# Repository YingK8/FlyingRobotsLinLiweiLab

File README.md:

# FlyingRobotsLinLiweiLab

A magnetically actuated micro flying robot. A four-coil phased array drives a
rotating field that spins and tilts a passive magnetic rotor; a stereo camera
rig closes the loop on its pose.

| Where | What |
|---|---|
| [`ESP32_PMW/`](ESP32_PMW/README.md) | ESP32 firmware: phased PWM coil drive, current sensing, balance loop |
| [`ESP32_PMW/controller/`](ESP32_PMW/controller/README.md) | the vision → control pipeline (camera → calib → pose → control) |
| `ESP32_PMW/ai/` | sweeps, system ID, validation, instrumentation, plotting |
| `PCB/`, `ESP32_PMW/docs/` | the H-bridge power stage: KiCad sources and the board writeup |
| `3DModels/` | printed frame, coil plate, takeoff rig |
| `calculations/` | coil resonance and capacitor sizing |
| `pico/` | earlier RP2040 current-characterization work (see `pico/PROGRESS.md`) |

Start with [`ESP32_PMW/README.md`](ESP32_PMW/README.md) for the firmware, or
[`ESP32_PMW/controller/README.md`](ESP32_PMW/controller/README.md) for the
control pipeline. Each controller stage carries its own `theory.md` chapter
deriving what it implements.

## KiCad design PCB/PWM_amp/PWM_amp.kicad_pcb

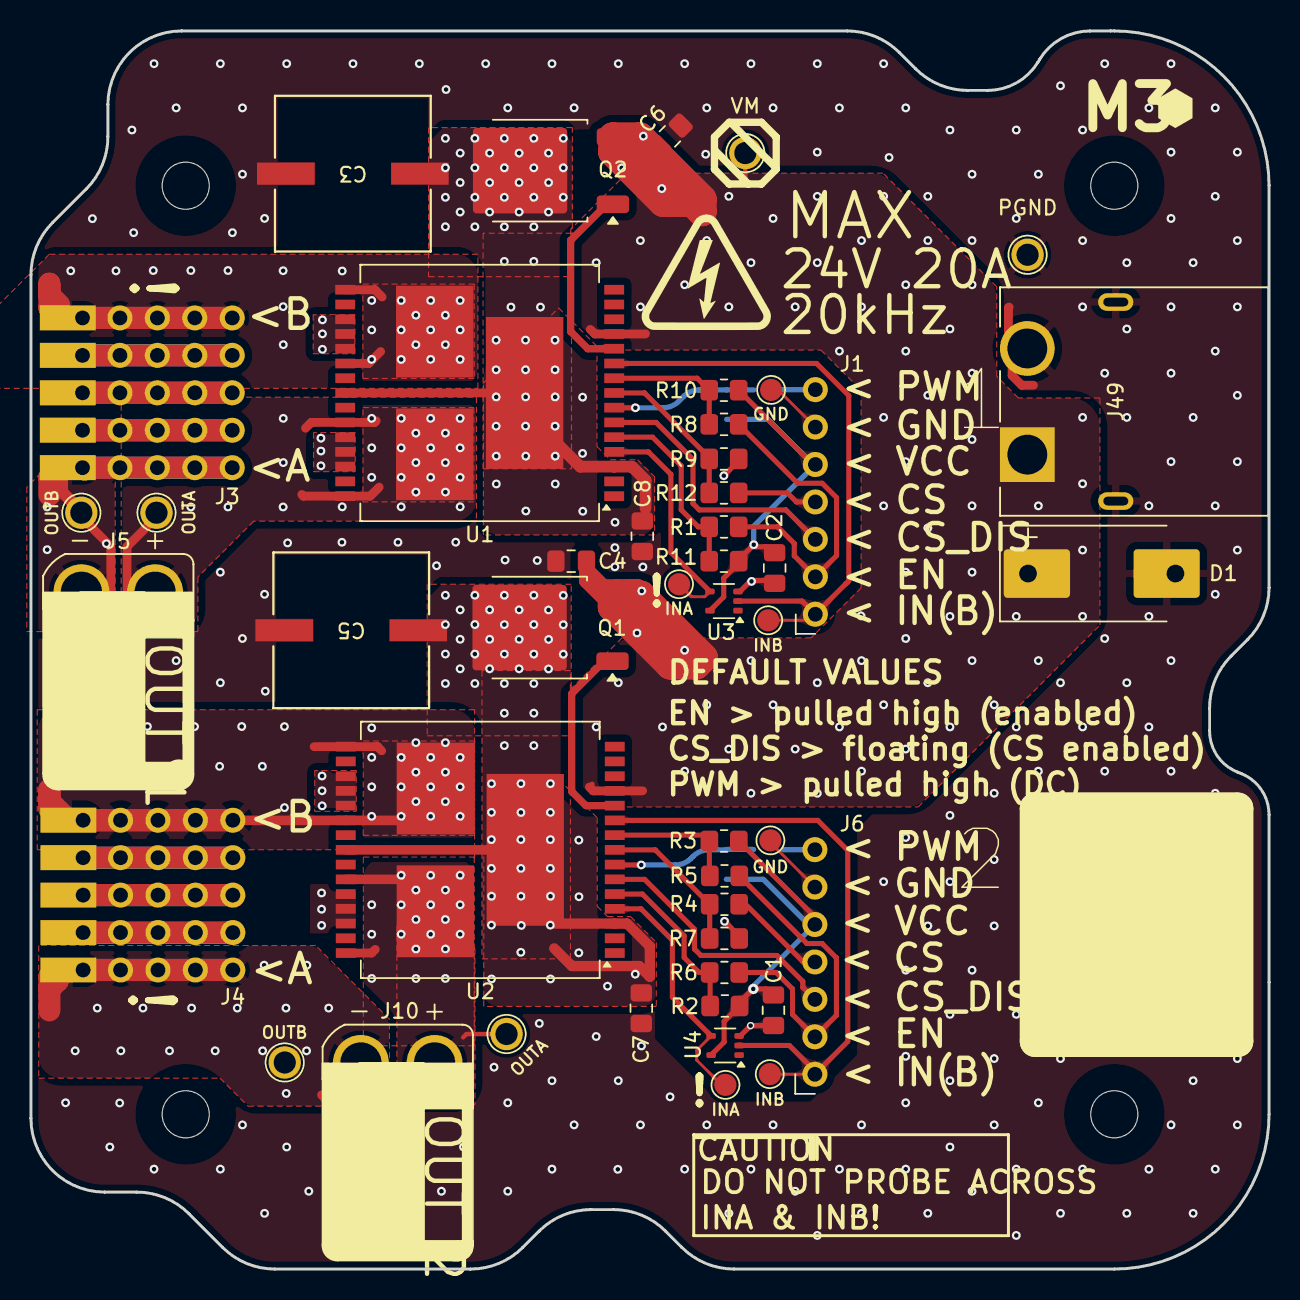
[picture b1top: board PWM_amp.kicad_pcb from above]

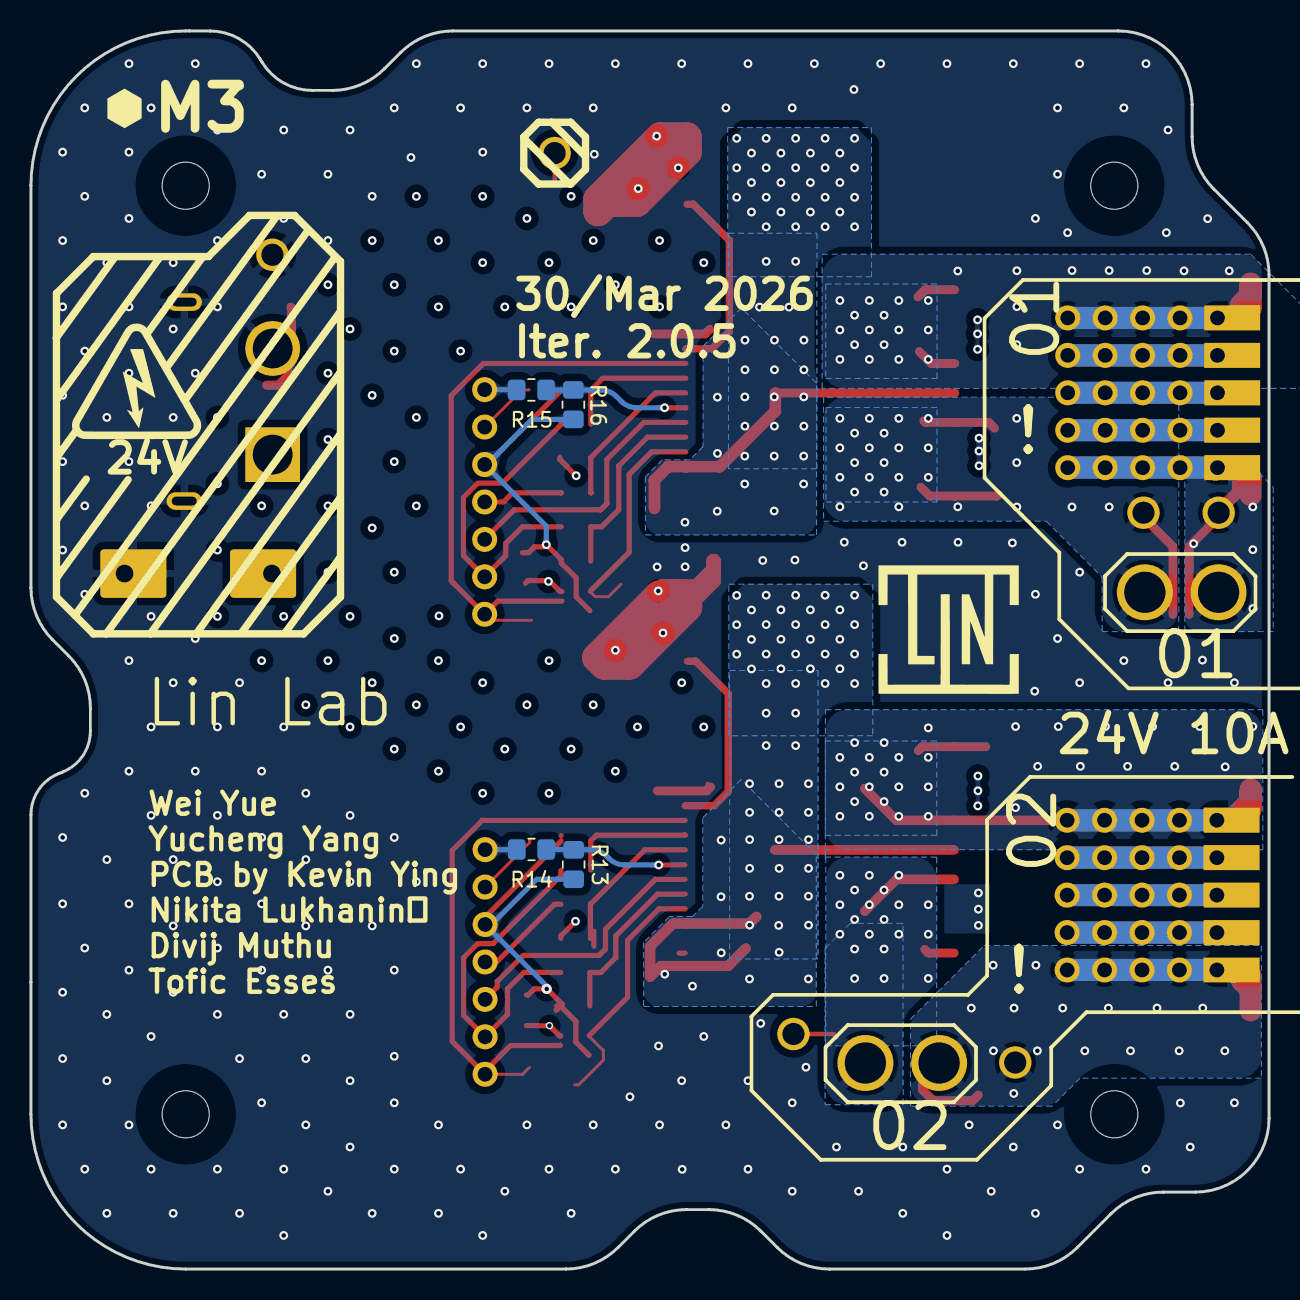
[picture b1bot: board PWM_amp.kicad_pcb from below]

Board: 4 copper layers, 84.0 x 84.0 mm, 54 parts (6 on the bottom side), 34 nets.

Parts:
C1, C2, C7, C8: 0.1uF; C_0805_2012Metric_Pad1.18x1.45mm_HandSolder
C3, C5: 100uF; CAP_EEH-ZC_10P3X10P3_PAN
C4, C6: 1uF; C_0805_2012Metric_Pad1.18x1.45mm_HandSolder
D1: SMCJ18A; D_SMC-RM10_Universal_Handsoldering
GND: TestPoint; TestPoint_Pad_D1.5mm
GND#2: TestPoint; TestPoint_Pad_D1.5mm
H1, H2, H3, H8: MountingHole; MountingHole_3.2mm_M3
INA: TestPoint; TestPoint_Pad_D1.5mm
INA#2: TestPoint; TestPoint_Pad_D1.5mm
INB: TestPoint; TestPoint_Pad_D1.5mm
INB#2: TestPoint; TestPoint_Pad_D1.5mm
J1, J6: Conn_01x07_Pin; PinSocket_1x07_P2.54mm_Vertical
J3, J4: Conn_01x02_Pin; matrix5x5
J5, J10: XT30UPB-M; xt30
J49: XT60PW-M; AMASS_XT60PW-M
OUTA: TestPoint; TestPoint_THTPad_D3.0mm_Drill1.5mm
OUTA#2: TestPoint; TestPoint_THTPad_D3.0mm_Drill1.5mm
OUTB: TestPoint; TestPoint_THTPad_D3.0mm_Drill1.5mm
OUTB#2: TestPoint; TestPoint_THTPad_D3.0mm_Drill1.5mm
PGND: TestPoint; TestPoint_THTPad_D3.0mm_Drill1.5mm
Q1, Q2: FDD8447L; TO-252-2
R1, R5, R6, R7, R8, R9: 1k; R_0805_2012Metric_Pad1.20x1.40mm_HandSolder
R2, R3, R4, R10, R11, R12, R13, R16: 4.7k; R_0805_2012Metric_Pad1.20x1.40mm_HandSolder
R14, R15: 100; R_0805_2012Metric_Pad1.20x1.40mm_HandSolder
U1, U2: VNH5019A-E; ST_MultiPowerSO-30
U3, U4: NC7SVU04P5X; SOT-353_SC-70-5
VM: TestPoint; TestPoint_THTPad_D3.0mm_Drill1.5mm

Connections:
+3V_1: C1.1, C2.1, J1.5, J6.5, R2.2, R3.2, R10.2, R11.2, R13.2, R16.2, U3.5 (VCC), U4.5 (VCC)
GND1: C1.2, C2.2, GND.1, GND#2.1, J1.6, J6.6, R7.1, R9.1, U3.3 (GND), U4.3 (GND)
INA1: INA.1, U2.4 (INA), U4.4
INA2: INA#2.1, U1.4 (INA), U3.4
INB1: INB.1, J6.1, U2.10 (INB), U4.2
INB2: INB#2.1, J1.1, U1.10 (INB), U3.2
unnamed: J1.2, R1.1, R8.1
unnamed: J1.3, U1.6 (CS_DIS)
unnamed: J1.4, R12.1
unnamed: J1.7, R15.1
unnamed: J3.1, U1.15 (OUTB), U1.16 (OUTB), U1.21 (OUTB), U1.32 (OUTB)
unnamed: J3.2, J5.N, OUTB.1
unnamed: J4.1, U2.15 (OUTB), U2.16 (OUTB), U2.21 (OUTB), U2.32 (OUTB)
unnamed: J4.2, J10.N, OUTB#2.1
unnamed: J5.P, OUTA.1, U1.1 (OUTA), U1.25 (OUTA), U1.30 (OUTA), U1.33 (OUTA)
unnamed: J6.2, R5.1, R6.1
unnamed: J6.3, U2.6 (CS_DIS)
unnamed: J6.4, R4.1
unnamed: J6.7, R14.1
unnamed: J10.P, OUTA#2.1, U2.1 (OUTA), U2.25 (OUTA), U2.30 (OUTA), U2.33 (OUTA)
unnamed: C5.1, C7.1, Q1.2 (D), U2.3 (VCC), U2.13 (VCC), U2.23 (VCC), U2.31 (VCC)
unnamed: Q1.1 (G), U2.11 (CP)
unnamed: C3.1, C8.1, Q2.2 (D), U1.3 (VCC), U1.13 (VCC), U1.23 (VCC), U1.31 (VCC)
unnamed: Q2.1 (G), U1.11 (CP)
unnamed: R9.2, R12.2, U1.8 (CS)
unnamed: R1.2, R11.1, U1.5 (EN/DIAGA)
unnamed: R8.2, R10.1, U1.9 (EN/DIAGB)
unnamed: R15.2, R16.1, U1.7 (PWM)
unnamed: R4.2, R7.2, U2.8 (CS)
unnamed: R2.1, R6.2, U2.5 (EN/DIAGA)
unnamed: R3.1, R5.2, U2.9 (EN/DIAGB)
unnamed: R13.1, R14.2, U2.7 (PWM)
PGND1: C3.2, C4.2, C5.2, C6.2, C7.2, C8.2, D1.2 (A), J49.2 (N), J49.SH1 (SHIELD), J49.SH2 (SHIELD), PGND.1, U1.18 (GNDB), U1.19 (GNDB), U1.20 (GNDB), U1.26 (GNDA), U1.27 (GNDA), U1.28 (GNDA), U2.18 (GNDB), U2.19 (GNDB), U2.20 (GNDB), U2.26 (GNDA), U2.27 (GNDA), U2.28 (GNDA)
VM1: C4.1, C6.1, D1.1 (K), J49.1, Q1.3 (S), Q2.3 (S), U1.12 (VBAT), U2.12 (VBAT), VM.1

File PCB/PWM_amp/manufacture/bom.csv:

Designator,Footprint,Quantity,Value,LCSC Part #
"C1, C2, C7, C8",0805,4,0.1uF,
"C3, C5",CAP_EEH-ZC_10P3X10P3_PAN,2,100uF,
"C4, C6",0805,2,1uF,
D1,D_SMC-RM10_Universal_Handsoldering,1,SMCJ18A,
INA1,TestPoint_Loop_D1.80mm_Drill1.0mm_Beaded,1,INB1,
INA2,TestPoint_Loop_D1.80mm_Drill1.0mm_Beaded,1,INB2,
INB1,TestPoint_Loop_D1.80mm_Drill1.0mm_Beaded,1,INA1,
INB2,TestPoint_Loop_D1.80mm_Drill1.0mm_Beaded,1,INA2,
"J1, J2",PinHeader_1x06_P2.54mm_Vertical,2,Conn_01x06_Pin,
"J10, J5",AMASS_XT30UPB-M,2,XT30UPB-M,
"J3, J4",matrix5x5,2,Conn_01x02_Pin,
J49,AMASS_XT60PW-M,1,XT60PW-M,
"OUT1_2, OUT1",TestPoint_Loop_D1.80mm_Drill1.0mm_Beaded,2,OUTB,
"OUT2_2, OUT2",TestPoint_Loop_D1.80mm_Drill1.0mm_Beaded,2,OUTA,
PGND,TestPoint_Loop_D1.80mm_Drill1.0mm_Beaded,1,GND1,
"Q1, Q2",TO-252-2,2,FDD8447L,
"R1, R5, R6, R7, R8, R9",0805,6,1k,
"R10, R11, R12, R2, R3, R4",0805,6,4.7k,
"U1, U2",ST_MultiPowerSO-30,2,VNH5019A-E,
"U3, U4",SOT-353_SC-70-5,2,NC7SVU04P5X,
VM,TestPoint_Loop_D1.80mm_Drill1.0mm_Beaded,1,VM1,

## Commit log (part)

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2025-10-19 draft code for 2 channel PMW
2025-10-19 added phase control
2025-10-21 new code for ATmega
2025-10-22 latest ATmega firmware
2025-10-31 6 channel maybe pmw?
2025-10-31 simplified PMW software-based generator
2025-11-03 no error displayed for pmw generation
2025-11-03 MILESTONE: basic functions mostly working
2025-11-03 minor formatting
2025-11-22 uploaded my stuff
2025-11-28 working code
2026-01-20 vibe coded multi-esp code
2026-01-29 working software-controlled pwm
2026-01-29 removed unused lib
2026-01-30 can change freq
2026-02-05 more change freuqnecy changes
2026-02-05 added frequency pause
2026-02-09 attempt to stream-line code
2026-02-09 added high-level library for real-time control and sync
2026-02-09 improved sync
2026-02-09 reduced sync time
2026-02-09 changed to ISR for sync
2026-02-09 changed ramp control logic
2026-02-09 replaced digital read/write with ESP IDF code
2026-02-09 debugged gpio inputs
2026-02-11 esp32 sync and phase tuning working!
2026-02-11 updated ramp code; improved frequency change smoothness, turned off sync flag in platformio.ini
2026-02-13 latest code for yucheng
2026-02-14 duty cycle fixed
2026-03-01 2 layer design
2026-03-09 3d models and PCB
2026-03-09 added new takeoff ramp profile
2026-03-09 modified duty cycle params
2026-03-18 V1 version
2026-03-18 V2 started
2026-03-24 code testing for V2
2026-03-24 restored to version with MOSFET
2026-03-24 reverted mosfet
2026-03-24 DONE DRAFT
2026-03-25 version v2.0.0
2026-03-26 2.0.1
2026-03-26 2.0.2 silkscreen edits
2026-03-26 generated prod files
2026-03-26 centre-aligned waves for beamforming
2026-03-27 ver 2.0.3: edge cut edits
2026-03-27 2.0.4 final touches
2026-03-30 2.0.5
2026-03-30 updated gitignore
2026-03-30 amplitude tuning with carrier freq working!
2026-04-11 added Serial carrier duty cycle tuning
2026-04-12 added task sequencing from JSON
2026-04-12 added direct waypoint trajectory planning
2026-04-12 cleaned up csv loader
2026-04-16 added_writeup
2026-04-17 added circuits
2026-04-17 more writeup
2026-04-17 writeup BOM
2026-04-17 docx
2026-04-17 fixed formula
2026-04-17 cleaned up schematic
2026-04-17 fixed up schematic credits
2026-04-17 updated credits
2026-04-17 updated writeup export to docx
2026-04-24 working
2026-04-24 two-side-tilt
2026-05-07 experiment double channel
2026-05-07 pin changes
2026-05-07 pin mod
2026-05-08 working again
2026-05-11 Adopt morphology-based ellipse segmentation pipeline
2026-05-12 increased contrast
2026-05-12 Stabilize ellipse fitting and clean unused notebook code; dual duty cycle graph
2026-05-12 Fix grayscale overlay alignment with clamped crop bounds
2026-05-12 Use binary mask overlays instead of grayscale in visualization
2026-05-12 single channel visualisation done
2026-05-12 started on precession compoensation
2026-05-12 reduced mask threshold
2026-05-12 fixed csv column access
2026-05-12 Plot segment averages from area-based tilt angle
2026-05-12 Use combined radial+azimuthal final angle in output and plot
2026-05-12 Use first-frame A0 and growth-aware area ratio for tilt
2026-05-12 area
2026-05-12 Overlay axis angle and length in tilt visualization plot
2026-05-12 area compensation possibly works
2026-05-12 Add segment variance error bars to angle plot
2026-05-12 Re-implement PCA minor-axis tilt with l0 and acos(l/l0)
2026-05-12 mostly working
2026-05-12 working？
2026-05-18 fixed resolution issue
2026-05-18 missed changes
2026-05-20 fixed?
2026-05-23 new code
2026-05-24 increased ramp time to 40secs
2026-06-15 pinout debug
2026-06-16 hw issue?
2026-06-19 2 channel 2 channel current
2026-06-19 cooking
2026-06-19 reverted temp calibration change
2026-06-24 camera visual servoing
2026-06-25 work
2026-06-29 data collected
2026-06-29 added DC
